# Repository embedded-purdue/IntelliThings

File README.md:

# IntelliThings

**An LLM-powered smart home companion system — from IoT to AIoT.**

Embedded Systems @ Purdue (ES@P) · Fall 2026 · ECE SPARK Challenge

---

## What we're building

Classic smart homes stop at IoT: sensors report data, but a person still has to hand-write
"if this, then that" automations. IntelliThings closes the loop — **sensors → AI → action** —
so an LLM agent reasons over live sensor data and decides what the home should do.

*Example:* the room is warmer than comfortable **and** someone is present → the agent
decides to cool the room → Home Assistant turns on the fan → the node's display shows
"Room was 28 °C, turned on the fan."

Unlike camera-based systems such as Xiaomi Miloco 2.0, IntelliThings uses low-cost,
privacy-preserving **environmental sensors**, needs **no local compute box** (reasoning runs
in a cloud agent), and is built on **open protocols end to end** — MQTT, Home Assistant, MCP.

## Current Python prototype

The runnable AI pipeline is in [`ai/main.py`](ai/main.py). It uses Home Assistant
Container and a separate Mosquitto container on the project Pi, fetches
Assist-exposed context through MCP, and calls OpenRouter directly. It saves JSON
recommendations, optionally executes a configured virtual turn-on action, and
updates `input_text.ai_summary_overall`. A systemd timer runs it every five minutes.

See [local pipeline setup](ai/README.md#current-local-python-pipeline) for the root
`.venv`, `.env`, and run commands. The Lambda deployment and retained display-message
publishing described below are the target design, not features of this local
Python pipeline yet.

## Target architecture

```
Desktop sensor nodes (ESP32-C6, no_std Rust with esp-hal + Embassy)
  7 sensors · 5" DWIN display · WS2812B LED bar
        │  Wi-Fi / MQTT                     ▲  retained AI message
        ▼  intellithings/<node_id>/sensors  │  intellithings/<node_id>/display
Raspberry Pi 5 — Home Assistant OS
  Mosquitto broker · MQTT entities · virtual devices · dashboard
        │  HA automation: HTTPS POST /ha-event    ▲  MCP tool calls (via Nabu Casa)
        ▼                                         │
AWS API Gateway → Lambda agent harness (MCP client) ── LLM via OpenRouter
        ▲
        └── /chat ◄── chat bot (Discord or Telegram — team decision)
```

The agent **decides**; Home Assistant's **MCP Server** is how the decision is executed.
Actions hit real devices where we have them and HA virtual devices (thermostat, lights, fan,
purifier, humidifier…) for the rest.

### Sensor node hardware

| Block | Part |
|---|---|
| MCU | ESP32-C6-DevKitC-1-N8 — on the dev rigs, then plugged into sockets on the custom PCB in the final nodes |
| I2C sensors | SHT41 (temp/RH) · SGP40 (VOC Index) · SCD41 (CO₂) · BH1750 (light) · VL53L0X (ToF distance) |
| UART / GPIO sensors | PMS5003 (PM1.0/2.5/10) · LD2410C mmWave presence (OUT pin) |
| Display | DWIN DMG80480T050_09WN — 5", 800×480, UART (TTL mode), DGUS, 12 V |
| Light output | WS2812B addressable LED bar (RMT) |
| Power | 12 V or 5 V wall adapter (chosen during PCB design) |

Build plan: an **emulator ESP32** (3 simulated nodes, for early AI testing) → **2 identical
breadboard rigs** (Rig H for Hardware, Rig S for Software) → **3 final nodes** on custom SMT
PCBs in 3D-printed enclosures.

## Tech stack

**Firmware** Rust (`no_std`, stable; minimum 1.95, edition 2024) · `esp-hal` 1.2.2 · `esp-rtos` 0.4 · Embassy async tasks/networking · `esp-radio` 1.0.0-beta.1
**Protocols** Wi-Fi · MQTT · MCP (Matter was dropped)
**Hub** Raspberry Pi 5 · Raspberry Pi OS + Docker · Home Assistant Container · Mosquitto container · Python agent (OpenRouter)
**Cloud** OpenRouter for the LLM · future option: AWS Lambda + API Gateway (HTTP API) · Nabu Casa remote access
**Hardware** KiCad · JLCPCB · 3D printing

## Documentation

Start with the Project Guideline — it's the single current reference, and it wins if any
other doc disagrees.

| Doc | Contents |
|---|---|
| [Project Guideline](docs/Project_Guideline.md) | What we're building, BOM and spending, subteams, timeline, open team decisions |
| [Collaboration Guidelines](docs/Collaboration_Guidelines.md) | Subteam roles, GitHub workflow, KiCad / firmware / AI collaboration rules, code review, hand-offs |
| [Firmware Architecture](software/Firmware_Architecture.md) | Earlier ESP-IDF design: shared state, display and LED drivers, MQTT topics, boot sequence; see the [firmware README](software/firmware/README.md) for the current Rust toolchain and implementation |
| [AI Agent Notes](ai/AI_Agent_Notes.md) | Agent harness, HA hand-off, OpenRouter + MCP client loop, hosting, chat bot, security |
| [Hardware Design Decisions](hardware/Hardware_BOM_Candidates.md) | Why each part was chosen and what was considered |
| [Full Parts List](hardware/Full_Parts_List.md) | Per-part specs: interface, voltage, output, quantity, source |

Shared contracts between subteams (pin map, MQTT schema, `/ha-event` format, AI message
format, …) are written in `docs/interfaces/` **before** anyone builds against them.

## Team

| Subteam | Size | Lead | Owns |
|---|---|---|---|
| **Hardware** | 7 | @LiamWatson-Purdue | Rigs, pin map, power, PCB, enclosure |
| **Software** | 9 | @LukeTuthill | ESP32-C6 firmware, display GUI, MQTT topic contract |
| **AI** | 6 | @ProgrammingJohn | Home Assistant, broker, entities, virtual devices, MCP Server, dashboard; the agent, prompts, model testing, chat bot |
| **AI — Emulator** | | @spicybutter (PM) | Emulator ESP32 — 3 simulated nodes for early AI testing |
| **PM** | 2 | @spicybutter · @rakkicow | Cross-team coordination; code owners on every path. @rakkicow also owns the display UI |

## Workflow

**Issue → Branch → Change → Test → Pull Request → Review → Merge.**

- **`main`** — protected, demo-ready. Only receives `dev` at milestones.
- **`dev`** — integration branch. Every PR targets `dev`.
- **Feature branches** — cut from `dev`, named `software/…`, `hardware/…`, `ai/…`, `docs/…` or `demo/…`.

Link the issue in the PR ("Closes #12") and say how you tested it. Full workflow in
[`CONTRIBUTING.md`](CONTRIBUTING.md).

```bash
git clone https://github.com/embedded-purdue/IntelliThings.git
cd IntelliThings
git checkout dev
```

## Repository layout

| Path | Owner | Contents |
|---|---|---|
| [`hardware/`](hardware/) | Hardware | KiCad project(s) + project-local libraries, enclosure CAD, datasheets · design decisions and parts list |
| [`software/`](software/) | Software | `firmware/` (Rust node firmware) · firmware architecture |
| [`ai/`](ai/) | AI | Local Python pipeline, prompts, MCP tools, broker setup and scheduling · `emulator/` · `ha/` and `cloud/` scaffolding · agent notes |
| [`demo/`](demo/) | @spicybutter (PM) | Demo mode for the ECE SPARK booth · `demo-master/` (ESP32-C3 + game buzzer firmware) |
| [`docs/`](docs/) | Everyone | Project Guideline, Collaboration Guidelines · `interfaces/` holds the shared contracts |

Never commit secrets — current firmware reads Wi-Fi credentials from the local, ignored
`software/firmware/.cargo/esp-config.toml` and embeds them at build time; cloud keys live in
AWS Secrets Manager / Lambda environment config.

## Timeline

11 Sunday work sessions (1:00–4:00 PM), Sept 6 – Dec 6. No sessions on Oct 11, Nov 22 or
Nov 29. Full per-subteam schedule in the
[Project Guideline §9](docs/Project_Guideline.md#9-timeline--sunday-work-sessions).

| Milestone | Date |
|---|---|
| Rigs built, emulator feeding HA ✓ | Sep 27 |
| MQTT schema agreed; LLM pipeline working ✓ | Oct 4 |
| All I2C sensors working; schematic; AI messages to the node displays ✓ | Oct 18 |
| PCB layout (DevKit + breakouts on sockets); final pin map | Oct 25 |
| PCB order (JLCPCB) | Nov 1 |
| 3 final nodes assembled and added to HA | Nov 15 |
| Full-system verification, ECE SPARK prep | Dec 6 |

## Collaboration

Research is encouraged and the design isn't locked in — if you find a better sensor, agent
design or dashboard approach, bring it up at a meeting or in Discord. A recap is posted in
Discord after every meeting.

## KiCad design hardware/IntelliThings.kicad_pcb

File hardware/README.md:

# Hardware — Hardware Subteam

Lead: **@LiamWatson-Purdue** · 7 people · owns **Rig H**

The breadboard rigs, the pin map, power design, the custom PCB and the 3D-printed
enclosure for the three final sensor nodes. Design reasoning:
[`Hardware_BOM_Candidates.md`](Hardware_BOM_Candidates.md) ·
per-part specs: [`Full_Parts_List.md`](Full_Parts_List.md) ·
spending and build plan: [Project Guideline §3 and §7](../docs/Project_Guideline.md).

## Scope

- Build **Rig H and Rig S from one wiring diagram** so they stay identical; own the pin map
  (shared with Software)
- Pre-power checks: DWIN display set to **TTL mode**, 8-pin pinout confirmed, LD2410C supply
  voltage confirmed
- Power design; measure real current draw on the rig
- Compare the two WS2812B strips and pick one for the final bar
- Final PCB: schematic → layout → design review → JLCPCB order → SMT assembly of **3 nodes**
- Enclosure design and 3D printing ×3

## The node

| Block | Part | Interface |
|---|---|---|
| MCU | ESP32-C6 (DevKitC-1-N8 on the rigs) | — |
| Temp/RH, VOC, CO₂, light, distance | SHT41, SGP40, SCD41, BH1750, VL53L0X | One I2C bus (0x44, 0x59, 0x62, 0x23, 0x29) |
| Particulates | PMS5003 | UART0, 9600 baud (+ optional SET pin) |
| Presence | LD2410C mmWave | GPIO (OUT pin only) |
| Display | DWIN DMG80480T050_09WN, 5", 12 V | UART1, 8-pin 2.0 mm connector |
| LED bar | WS2812B | RMT, one data line via 3.3 → 5 V level shifter |

**7–8 pins, 2 UARTs.** On the DevKitC-1 avoid GPIO12/13 (USB-JTAG) and 16/17 (UART bridge);
don't put the LED data line or LD2410C OUT on strapping pins GPIO4, 5, 8, 9, 15.

## Power

Rails: **12 V** display · **5 V** PMS5003, LD2410C, LED bar · **3.3 V** ESP32-C6 + I2C sensors.
Input is 12 V (buck to 5 V) or 5 V (boost to 12 V for the display) — chosen during PCB
design. The **LED bar dominates the 5 V budget** (~60 mA per LED at full white). Common
ground everywhere.

## Final PCB

- **MCU:** bare ESP32-C6 chip if time allows; **fallback:** the DevKit plugged into female
  headers (or soldered to male headers). Decided at the **Oct 25** layout session — switch
  to the fallback rather than slip the order.
- **Option:** split into sensor / ESP / connector-power boards (each its own KiCad project;
  board-to-board pinouts become contracts in `docs/interfaces/`).
- Copy pull-ups, decoupling and regulators from the Adafruit breakout reference designs.

**Placement rules:** SHT41 and SCD41 away from heat (ESP32, converters, backlight) · clear
PMS5003 air inlet and outlet · windows for VL53L0X and BH1750 · no metal or ground pour in
front of the LD2410C · antenna keep-out for the bare chip or DevKit.

**Dates:** schematic by **Oct 18** · layout by **Oct 25** · design review and **JLCPCB order
Nov 1** (~7 days to DHL delivery, +~1 day with a stencil) · 3 nodes assembled by **Nov 15**.

## KiCad collaboration

- One board, one KiCad project, split into hierarchical sheets: **Power · MCU · I/O**.
- Each sheet has one owner at a time (assigned through Issues). **Never two people on the
  same sheet at once.**
- Keep every symbol and footprint in project-local libraries under `hardware/`.
- **Agree before changing:** GPIO assignments, I2C addresses, UART use, voltage levels,
  power requirements, connector types and pinouts, board placement.
- Layout: review the schematic together, confirm footprints and stock, 2–3 people route,
  everyone else reviews datasheets/footprints/DRC, **final team design review before
  ordering**.

## What to commit

**Yes:** schematics, layouts, CAD source, BOMs, datasheets.
**No:** gerbers, STLs, autosave/backup files — all re-exportable, all gitignored.
Anything over ~10 MB, ask in Discord first.

Branches: `hardware/power-input`, `hardware/mcu-bare-chip`, `hardware/io-sensor-bus`,
`hardware/led-bar`. See [`CONTRIBUTING.md`](../CONTRIBUTING.md).

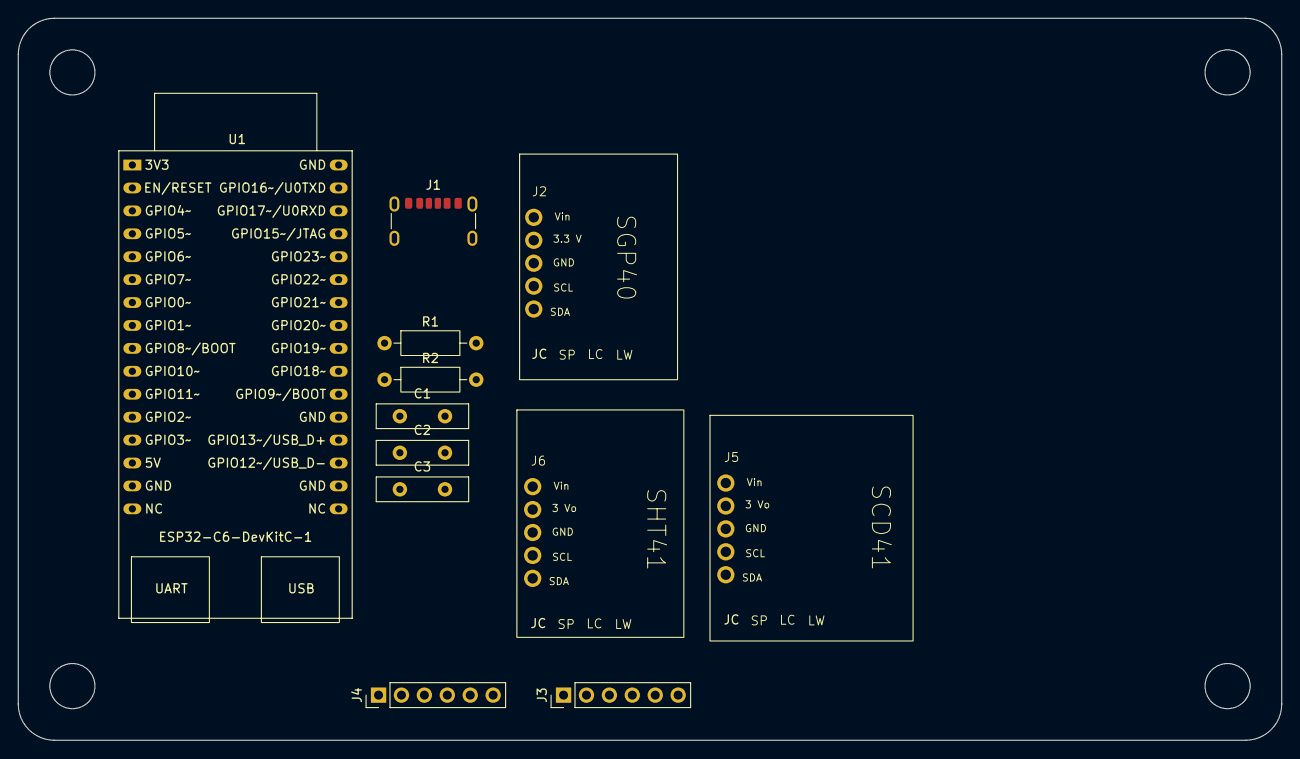
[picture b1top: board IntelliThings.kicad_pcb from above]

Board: 2 copper layers, 140.0 x 80.0 mm, 12 parts (0 on the bottom side), 6 nets, no tracks yet.

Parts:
C1: 10uF; C_Disc_D10.0mm_W2.5mm_P5.00mm
C2: 0.1uF; C_Disc_D10.0mm_W2.5mm_P5.00mm
C3: 10pF; C_Disc_D10.0mm_W2.5mm_P5.00mm
J1: USB_C_Receptacle_PowerOnly_6P; USB_C_Receptacle_GCT_USB4125-xx-x-0190_6P_TopMnt_Horizontal
J2: SGP40; SGP40 Footprint
J3: BH1750; PinHeader_1x06_P2.54mm_Vertical
J4: VL53L0X; PinHeader_1x06_P2.54mm_Vertical
J5: SCD41; SCD41 Footprint
J6: SHT41; SHT41 Footprint
R1, R2: 5.1k; R_Axial_DIN0207_L6.3mm_D2.5mm_P10.16mm_Horizontal
U1: ESP32-C6-DevKitC-1

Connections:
+5V: C1.2, C2.2, C3.2, J1.A9 (VBUS), J1.B9 (VBUS), J2.1, J3.1, J4.1, J5.1, J6.1, U1.14 (5V)
/SCL: J2.4, J3.4, J4.3, J5.4, J6.4, U1.6 (GPIO7)
/SDA: J2.5, J3.5, J4.4, J5.5, J6.5, U1.5 (GPIO6)
GND: C1.1, C2.1, C3.1, J1.A12 (GND), J1.B12 (GND), J1.SH (SHIELD), J2.3, J3.3, J4.2, J5.3, J6.3, R1.2, R2.2, U1.15 (GND), U1.18 (GND), U1.21 (GND), U1.32 (GND)
unnamed: J1.A5 (CC1), R1.1
unnamed: J1.B5 (CC2), R2.1
